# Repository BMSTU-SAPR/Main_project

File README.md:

## Main_project
Главный проект. Здесь будут собраны все работы

#Рыжков В.П. БМТ2-31М

## Отчет

Требуется создать схему электрическую-принципиальную платы, трассировку печатной платы и файлы платы для дальнейшего производства. Создание схемы происходит в программе KiCAD.

Плата будет основана на материалах, усвоенных в процессе прохождения курса и представлять из себя будет полосно-пропускающий фильтр на 2-х операционных усилителях. В целях возможности тестирования данной схемы при ее реальном производстве предусмотрены входы для осциллографа.

Поиск посадочных мест, УГО и 3D моделей элементов осуществлялось на сайтах https://www.snapeda.com/ и https://componentsearchengine.com/

В KiCAD были созданы отдельные библиотеки УГО и посадочных мест.

После этого с использованием новых компонентов была собрана схема электрической цепи (СЭП). Для стандартных элементов, таких как резисторы и конденсаторы, были выбраны площадки из библиотек KiCad. 

Затем проводим проверку получившейся СЭП и исправляем обнаруженные ошибки, связанные с подключением пинов, наличию "земли" у каждой микросхемы и др.

Собранная СЭП представлена на рис. 2.

Далее производим разводку печатной платы.

Далее нажимаем "Обновить печатную плату" и получаем печатную плату, после чего производим её разводку. Сначала соединяем контакты, не относящиеся к питанию и земле. Потом проводим питание, и в конце проводим землю. Для избежания перегрева и перегорания дорожек питания были рассчитаны ширины дорожек питания с помощью встроенного калькулятора для силы тока 0.5 Ампер. После проведения дорожек были скорректированы размеры печатной платы и произведена заливка платы GND с обеих сторон. При данной сложности схемы двуслойная плата - достаточна. Более того, оборотный ее слой задействовал в малой степени.

Для всех элементов платы, взятых с сайтов SnapEda и ComponentSearchEngine были выбраны 3D модели.

3D модель печатной платы представлена на следующих изображениях:

Рисунок 6 - Вид платы в 3д

Далее создаем гербер файлы и файлы сверловки.

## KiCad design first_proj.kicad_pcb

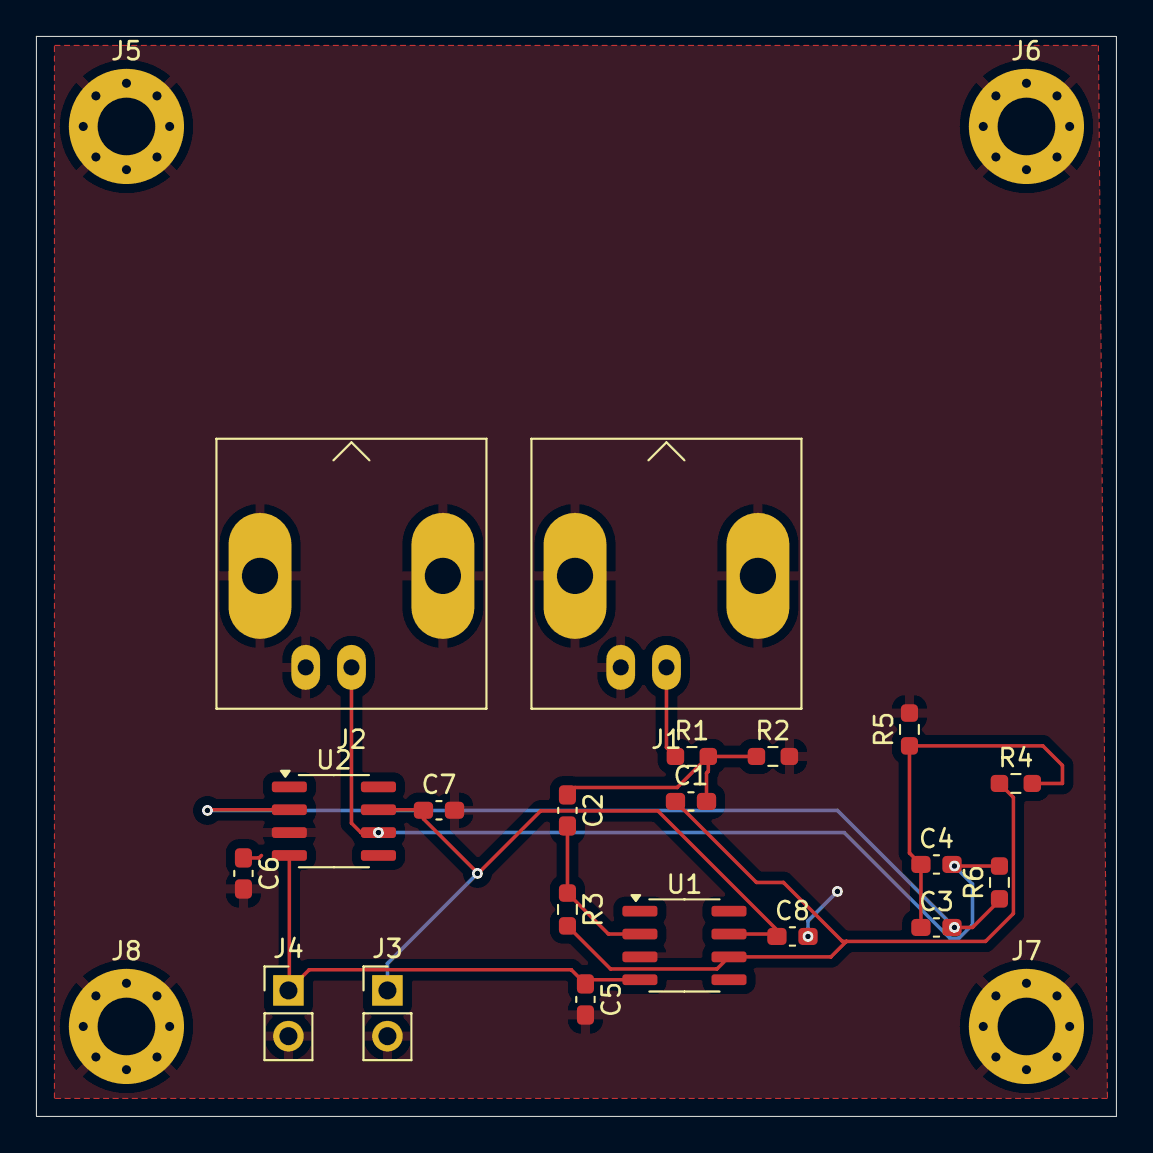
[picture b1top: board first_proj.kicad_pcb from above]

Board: 2 copper layers, 60.0 x 60.0 mm, 24 parts (0 on the bottom side), 10 nets.

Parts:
C1: 100p; C_0603_1608Metric_Pad1.08x0.95mm_HandSolder
C2, C3, C5, C6, C7, C8: 10n; C_0603_1608Metric_Pad1.08x0.95mm_HandSolder
C4: 12n; C_0603_1608Metric_Pad1.08x0.95mm_HandSolder
J1, J2: Conn_Coaxial; BNC_Amphenol_B6252HB-NPP3G-50_Horizontal
J3, J4: Conn_01x02; PinHeader_1x02_P2.54mm_Vertical
J5, J6, J7, J8: Screw_Terminal_01x01; MountingHole_3.2mm_M3_Pad_Via
R1: 1k; R_0603_1608Metric_Pad0.98x0.95mm_HandSolder
R2, R4: 10k; R_0603_1608Metric_Pad0.98x0.95mm_HandSolder
R3: 1.1k; R_0603_1608Metric_Pad0.98x0.95mm_HandSolder
R5, R6: 12k; R_0603_1608Metric_Pad0.98x0.95mm_HandSolder
U1, U2: OPA188xxD; SOIC-8_3.9x4.9mm_P1.27mm

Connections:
+5V: C7.1, C8.1, J3.1, U1.7 (V+), U2.7 (V+)
-5V: C5.1, J4.1, U1.4 (V-), U2.4 (V-)
GND: C5.2, C6.2, C7.2, C8.2, J1.2 (Ext), J2.2 (Ext), J3.2, J4.2, J5.1, J6.1, J7.1, J8.1, R2.2, R5.2, U1.3 (+), U2.3 (+)
unnamed: C1.1, R3.2, R4.1, U1.6
unnamed: C1.2, C2.1, R1.2, R2.1
unnamed: C3.1, C4.1, R4.2, R5.1
unnamed: J1.1 (In), R1.1
unnamed: C4.2, J2.1 (In), R6.2, U2.6
unnamed: C2.2, R3.1, U1.2 (-)
unnamed: C3.2, R6.1, U2.2 (-)

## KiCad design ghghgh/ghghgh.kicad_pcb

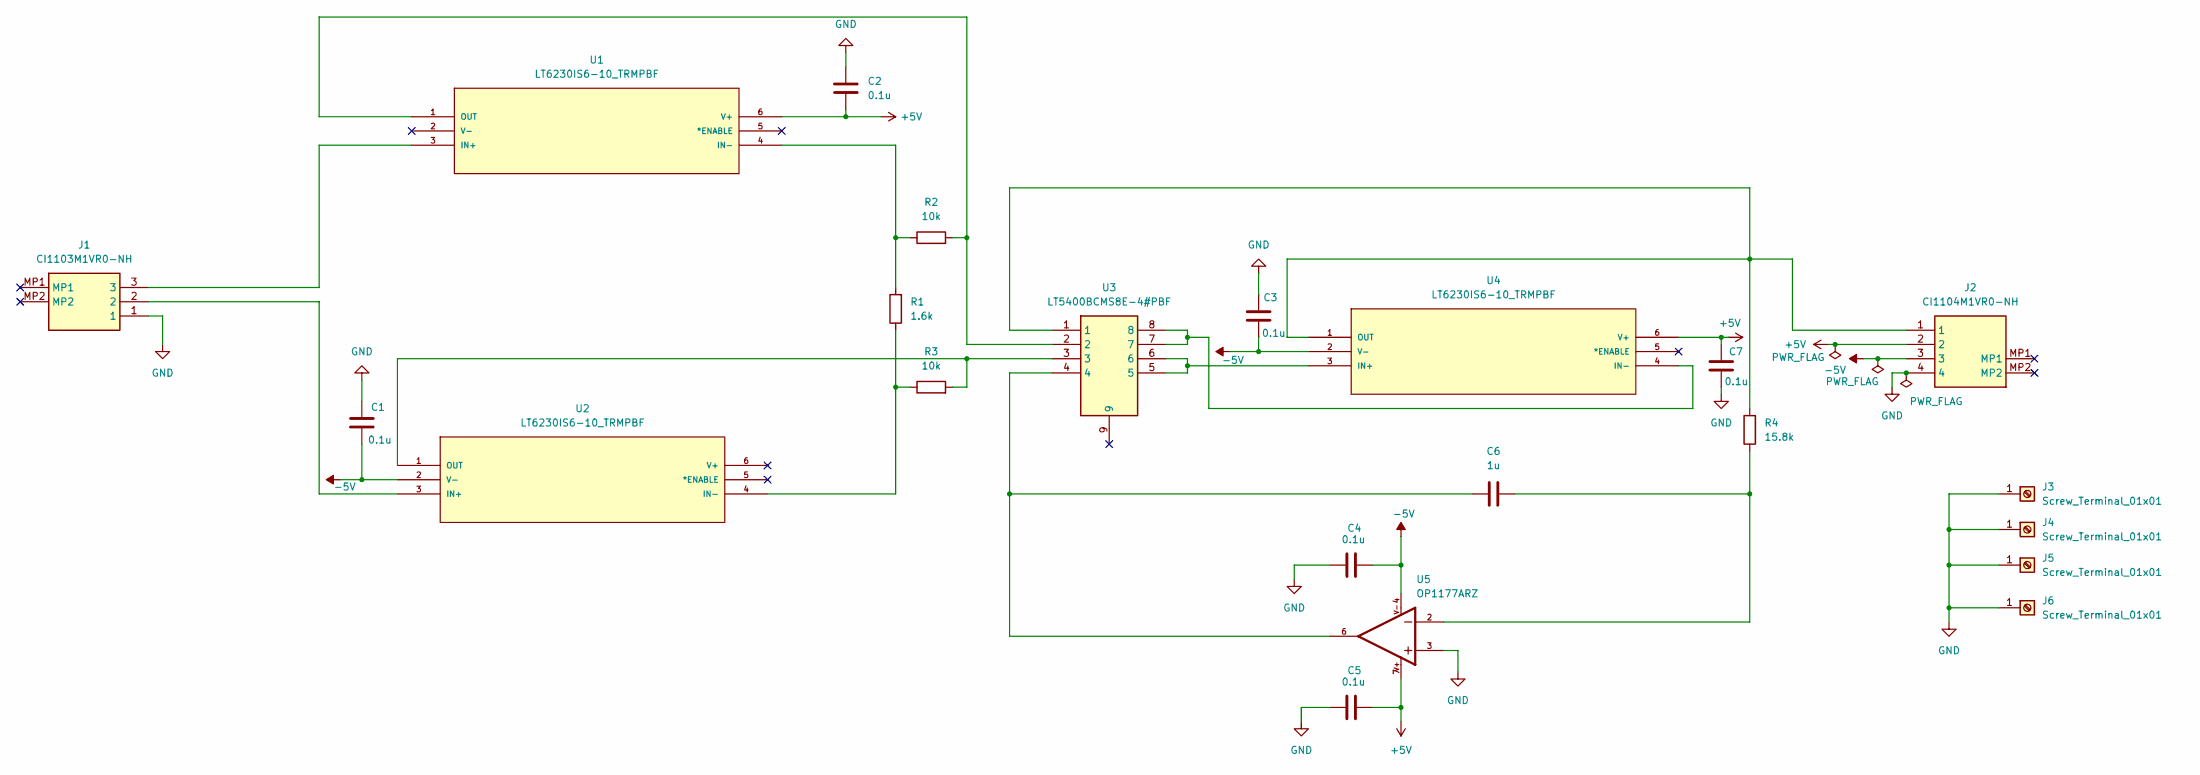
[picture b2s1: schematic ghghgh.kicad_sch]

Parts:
C1, C2, C3, C4, C5, C7: 0.1u; C_0201_0603Metric
C6: 1u; C_0201_0603Metric
J1: CI1103M1VR0-NH; CI1103M1VR0NH; Manufacturer_Part_Number CI1103M1VR0-NH
J2: CI1104M1VR0-NH; CI1104M1VR0NH; Manufacturer_Part_Number CI1104M1VR0-NH
J3, J4, J5, J6: Screw_Terminal_01x01; MountingHole_3mm_Pad_Via
R1: 1.6k; R_0201_0603Metric
R2, R3: 10k; R_0201_0603Metric
R4: 15.8k; R_0201_0603Metric
U1, U2, U4: LT6230IS6-10_TRMPBF; SOT-6_S
U3: LT5400BCMS8E-4#PBF; SOP65P490X110-9N; Manufacturer_Part_Number LT5400BCMS8E-4#PBF; Mouser Part Number 584-5400BCMS8E-4PBF
U5: OP1177ARZ; SO-8

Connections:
+5V: C2.1, C5.2, C7.2, J2.2, U1.6 (V+), U4.6 (V+), U5.7
-5V: C1.1, C3.1, C4.2, J2.3, U2.2 (V-), U4.2 (V-), U5.4
GND: C1.2, C2.2, C3.2, C4.1, C5.1, C7.1, J1.1, J2.4, J3.1, J4.1, J5.1, J6.1, U5.3
unnamed: C6.1, U3.4, U5.6
unnamed: C6.2, R4.1, U5.2
unnamed: J1.3, U1.3 (IN+)
unnamed: R1.2, R2.1, U1.4 (IN-)
unnamed: R2.2, U1.1 (OUT), U3.2
unnamed: J1.2, U2.3 (IN+)
unnamed: R1.1, R3.1, U2.4 (IN-)
unnamed: R3.2, U2.1 (OUT), U3.3
unnamed: U3.5, U3.6, U4.3 (IN+)
unnamed: U3.7, U3.8, U4.4 (IN-)
unnamed: J2.1, R4.2, U3.1, U4.1 (OUT)

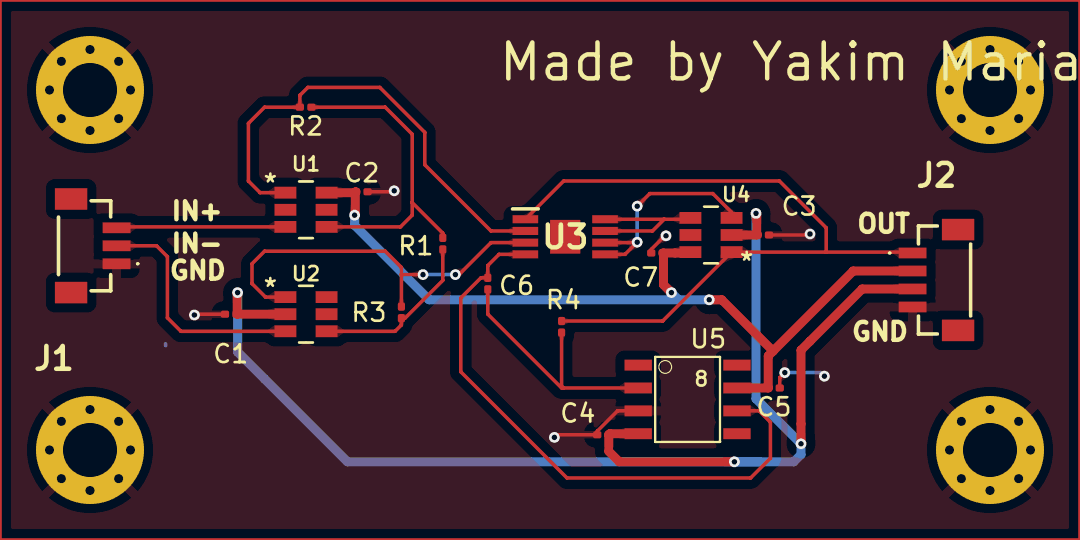
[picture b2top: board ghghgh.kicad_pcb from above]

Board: 2 copper layers, 22 parts (0 on the bottom side), 14 nets.

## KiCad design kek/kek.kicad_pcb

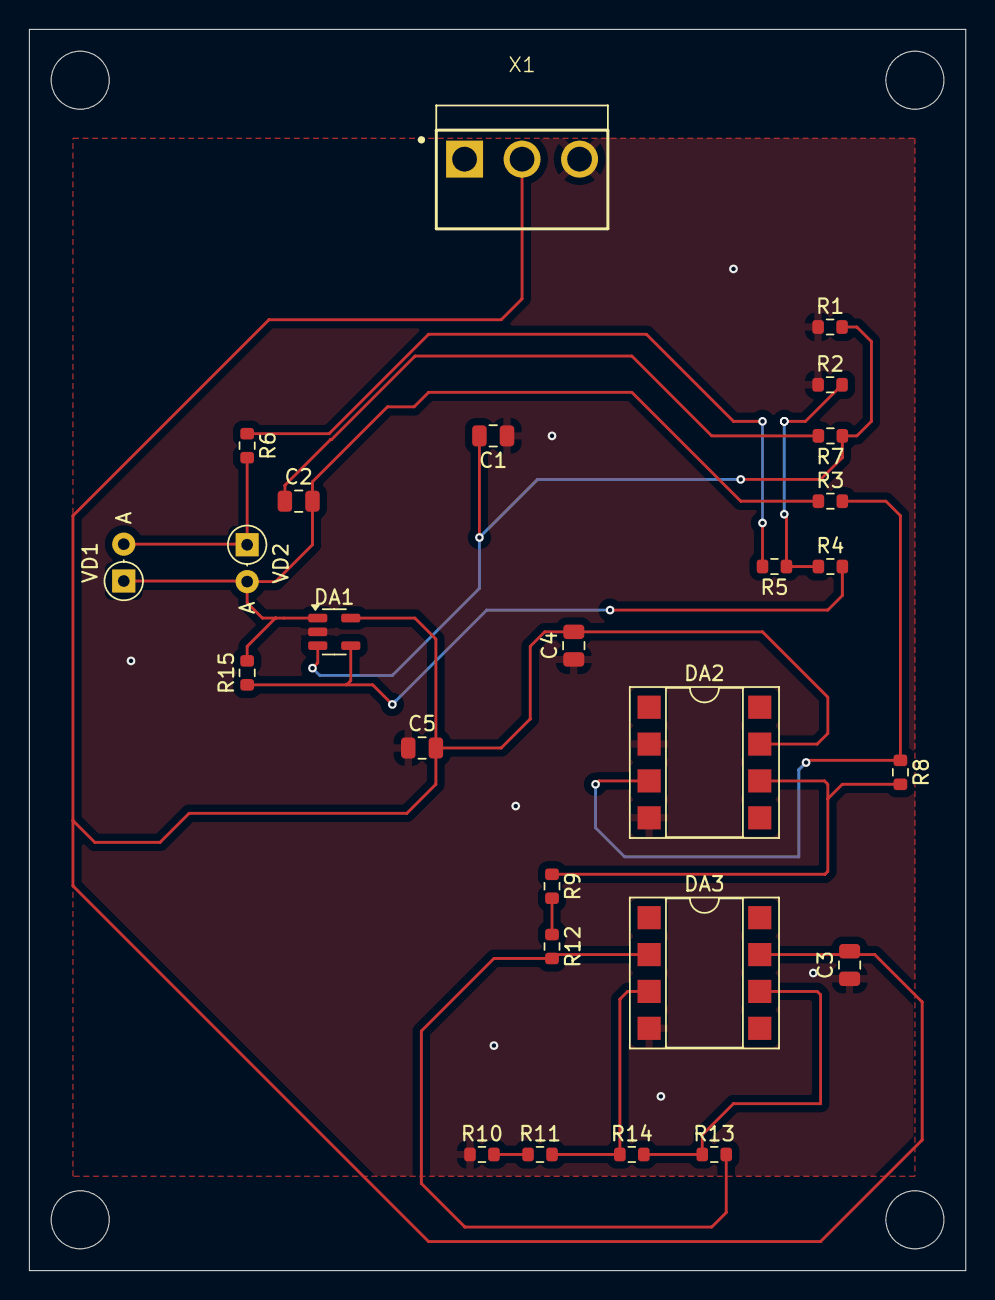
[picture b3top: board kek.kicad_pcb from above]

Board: 2 copper layers, 64.5 x 85.5 mm, 26 parts (0 on the bottom side), 16 nets.

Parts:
C1, C2: 750p; C_0805_2012Metric
C3, C4, C5: 0.1u; C_0805_2012Metric
DA1: AD8616; SOT-23-5
DA2, DA3: OP27; DIP-8_W7.62mm_SMDSocket_SmallPads
R1, R6, R7: 2.2k; R_0603_1608Metric
R2, R9, R10: 220; R_0603_1608Metric
R3: 10k; R_0603_1608Metric
R4: 100k; R_0603_1608Metric
R5: 160; R_0603_1608Metric
R8: 51k; R_0603_1608Metric
R11, R12: 5.1; R_0603_1608Metric
R13, R14: 1k; R_0603_1608Metric
R15: 220k; R_0603_1608Metric
VD1, VD2: 1N4148; D_DO-35_SOD27_P2.54mm_Vertical_AnodeUp
X1: B3P-VH

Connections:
+5V: C3.2, C4.2, C5.2, DA1.5 (V+), DA2.7 (V+), DA3.7 (V+), X1.2
/OUT1: C2.2, DA1.1 (OUT), R3.1, R15.2, VD1.1, VD2.2
/OUT2: DA2.6 (OUT), R8.2, R9.1
Earth: C1.1, C3.1, C4.1, C5.1, DA1.2 (V-), DA2.2 (IN+), DA2.4 (V-), DA3.4 (V-), R1.1, R2.1, R10.1, X1.3
unnamed: C2.1, R7.2
unnamed: C1.2, DA1.3 (IN+), R1.2, R7.1
unnamed: DA1.4 (IN-), R4.2, R15.1
unnamed: DA2.3 (IN-), R3.2, R8.1
unnamed: DA3.2 (IN+), R12.2, R13.2
unnamed: DA3.3 (IN-), R11.2, R14.1
unnamed: DA3.6 (OUT), R13.1, R14.2
unnamed: R2.2, R4.1, R5.1
unnamed: R5.2, R6.1
unnamed: R6.2, VD1.2, VD2.1
unnamed: R10.2, R11.1
unnamed: R9.2, R12.1

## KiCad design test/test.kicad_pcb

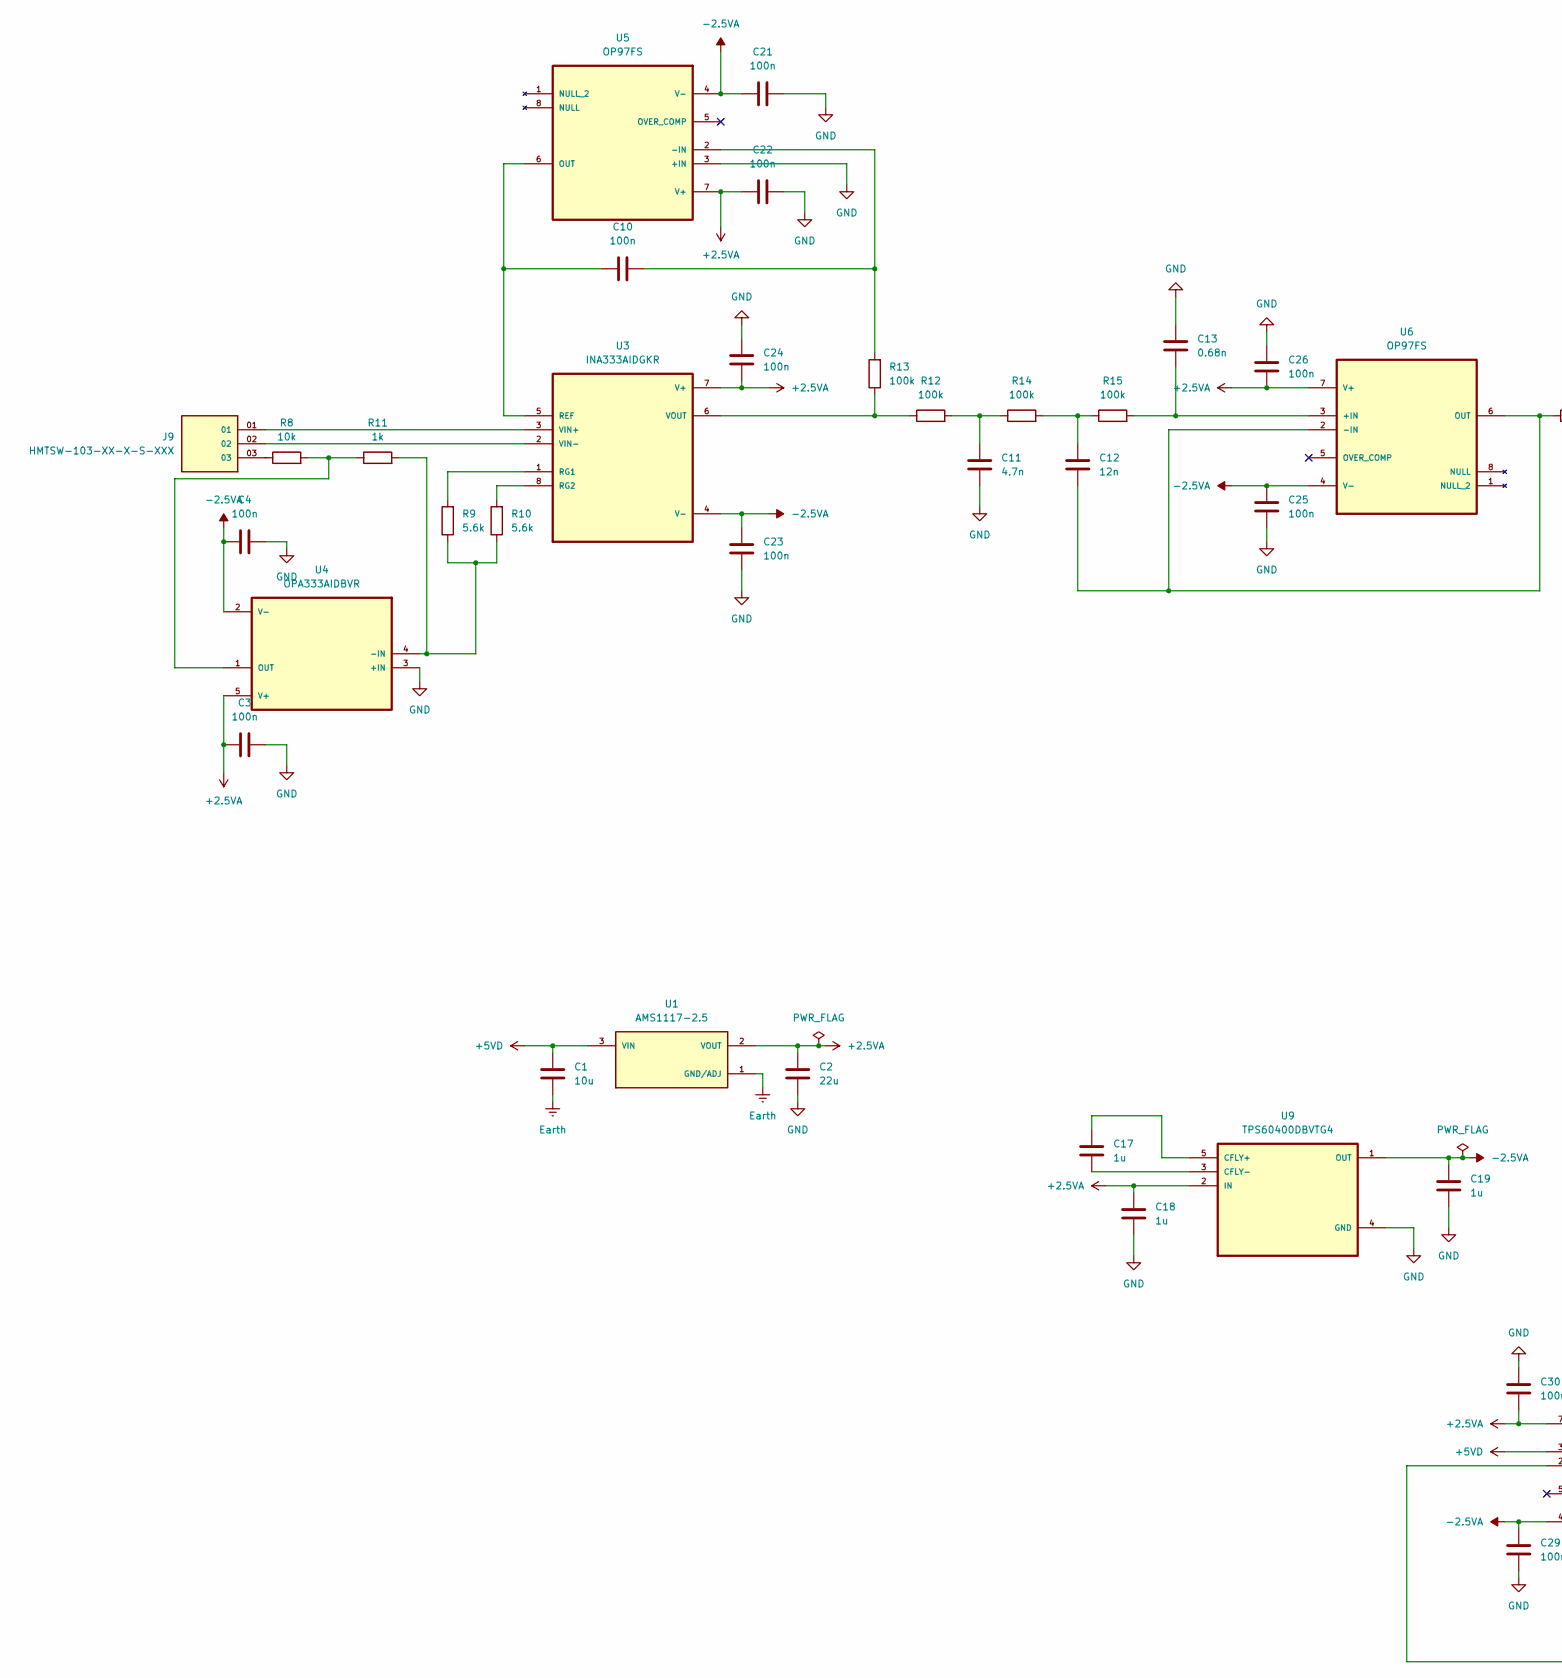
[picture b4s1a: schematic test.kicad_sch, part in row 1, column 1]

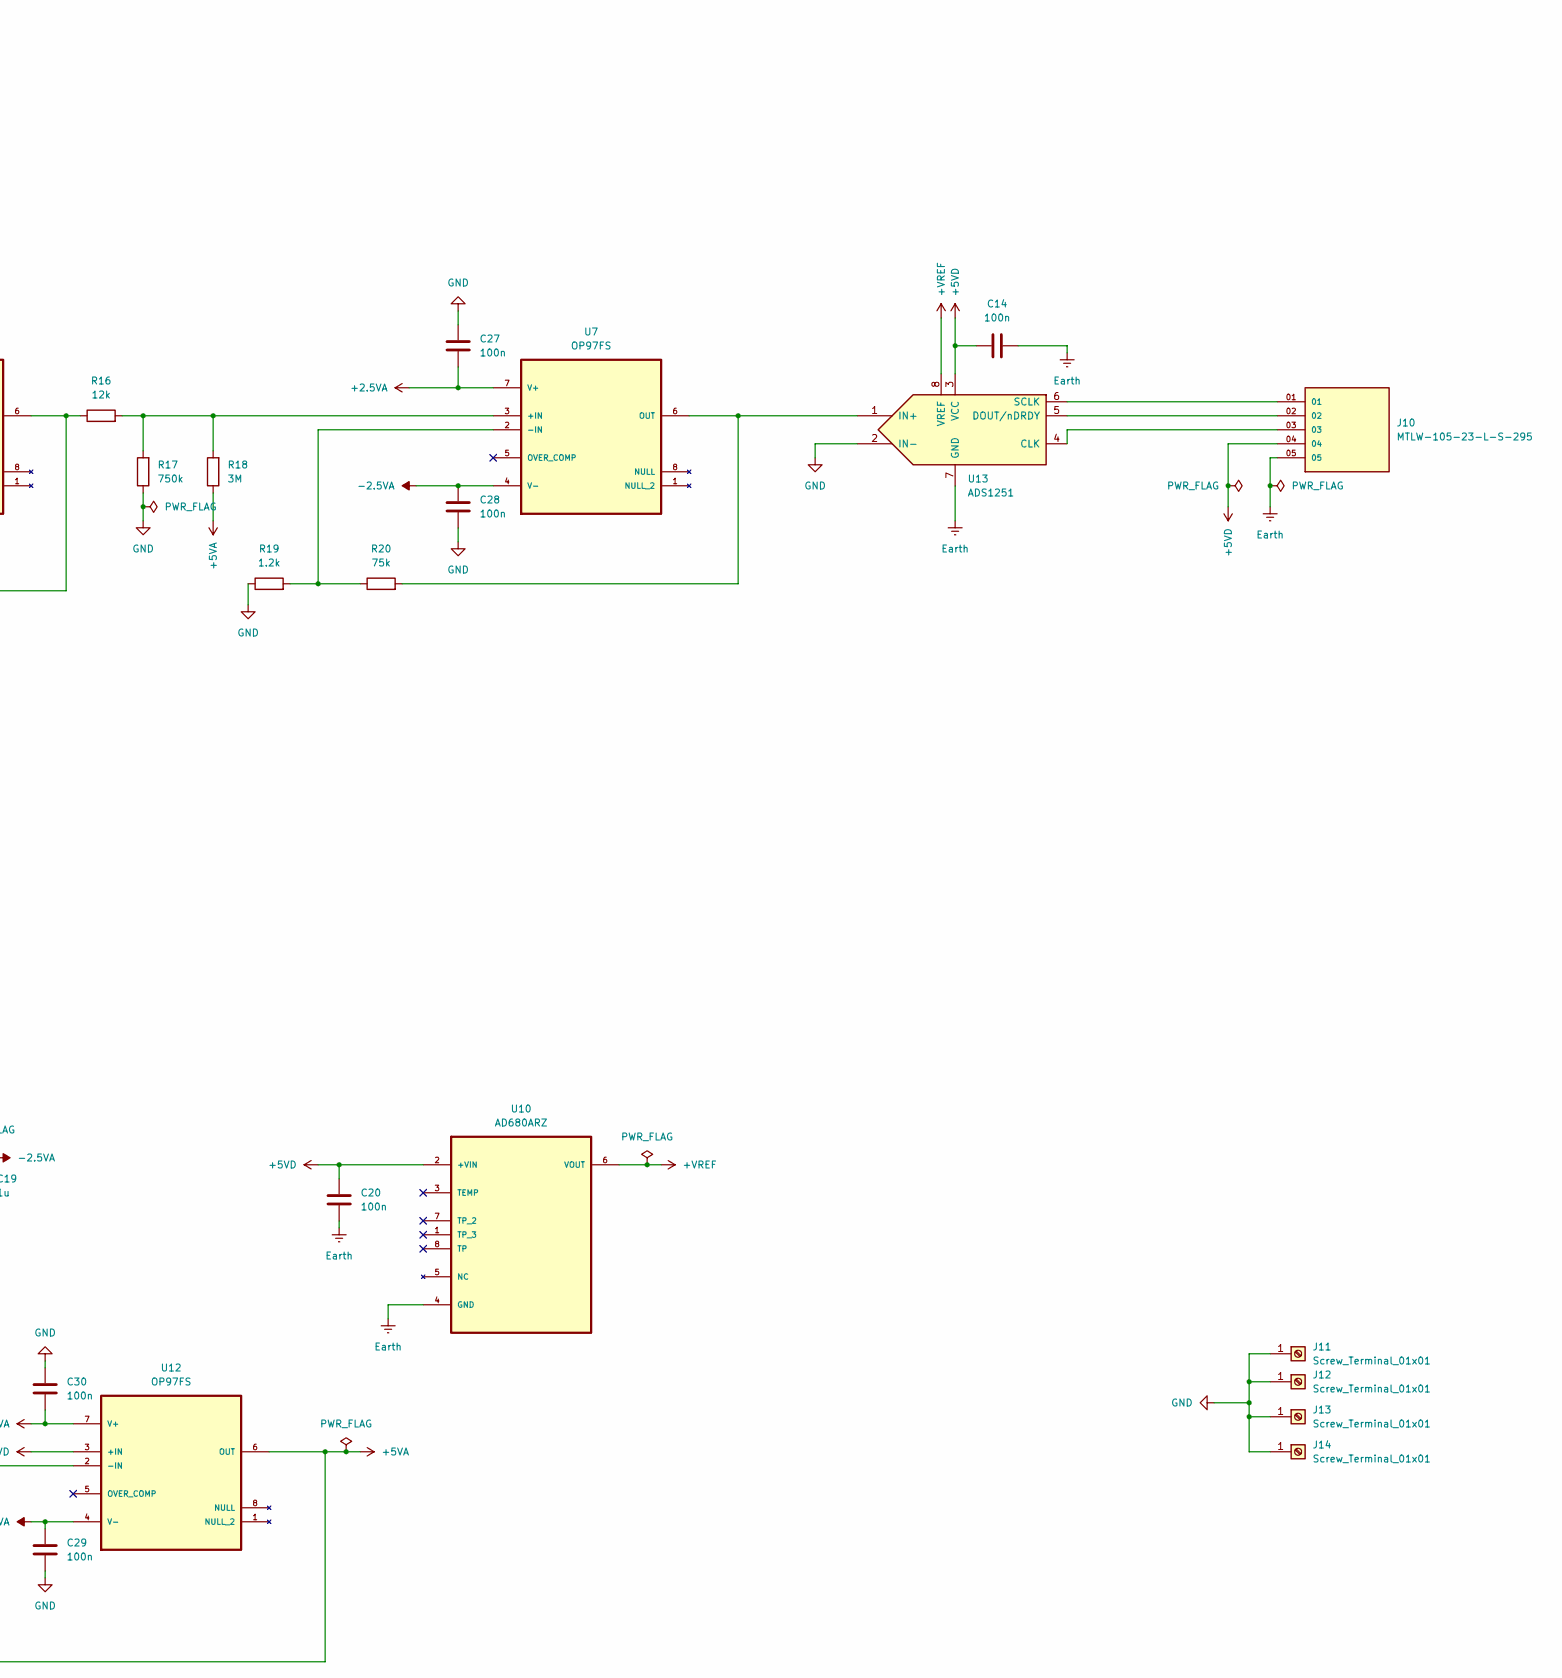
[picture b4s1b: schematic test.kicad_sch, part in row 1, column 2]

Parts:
C1: 10u; C_0201_0603Metric
C2: 22u; C_0201_0603Metric
C3, C4, C10, C14, C20, C21, C22, C23, C24, C25, C26, C27, C28, C29, C30: 100n; C_0201_0603Metric
C11: 4.7n; C_0201_0603Metric
C12: 12n; C_0201_0603Metric
C13: 0.68n; C_0201_0603Metric
C17, C18, C19: 1u; C_0201_0603Metric
J9: HMTSW-103-XX-X-S-XXX; SAMTEC_HMTSW-103-XX-X-S-XXX; PARTREV A
J10: MTLW-105-23-L-S-295; SAMTEC_MTLW-105-23-L-S-295; PARTREV R
J11, J12, J13, J14: Screw_Terminal_01x01; MountingHole_3.2mm_M3_Pad_Via
R8: 10k; R_0201_0603Metric
R9, R10: 5.6k; R_0201_0603Metric
R11: 1k; R_0201_0603Metric
R12, R13, R14, R15: 100k; R_0201_0603Metric
R16: 12k; R_0201_0603Metric
R17: 750k; R_0201_0603Metric
R18: 3M; R_0201_0603Metric
R19: 1.2k; R_0201_0603Metric
R20: 75k; R_0201_0603Metric
U1: AMS1117-2.5; SOT229P700X180-4N; PARTREV N/A
U3: INA333AIDGKR; SOP65P490X110-8N
U4: OPA333AIDBVR; SOT95P280X145-5N
U5, U6, U7, U12: OP97FS; SOIC127P600X175-8N-1; MPN OP97FS
U9: TPS60400DBVTG4; SOT95P280X145-5N
U10: AD680ARZ; SOIC127P600X175-8N; MPN AD680ARZ
U13: ADS1251; SOIC-8_3.9x4.9mm_P1.27mm

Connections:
+2.5VA: C2.2, C3.1, C18.2, C22.1, C24.1, C26.1, C27.1, C30.1, U1.2 (VOUT), U3.7 (V+), U4.5 (V+), U5.7 (V+), U6.7 (V+), U7.7 (V+), U9.2 (IN), U12.7 (V+)
+5VA: R18.1, U12.2 (-IN), U12.6 (OUT)
+5VD: C1.2, C14.1, C20.2, J10.04, U1.3 (VIN), U10.2 (+VIN), U12.3 (+IN), U13.3 (VCC)
+VREF: U10.6 (VOUT), U13.8 (VREF)
-2.5VA: C4.1, C19.2, C21.1, C23.2, C25.2, C28.2, C29.2, U3.4 (V-), U4.2 (V-), U5.4 (V-), U6.4 (V-), U7.4 (V-), U9.1 (OUT), U12.4 (V-)
Earth: C1.1, C14.2, C20.1, J10.05, U1.1 (GND/ADJ), U10.4 (GND), U13.7 (GND)
GND: C2.1, C3.2, C4.2, C11.1, C13.2, C18.1, C19.1, C21.2, C22.2, C23.1, C24.2, C25.1, C26.2, C27.2, C28.1, C29.1, C30.2, J11.1, J12.1, J13.1, J14.1, R17.1, R19.1, U4.3 (+IN), U5.3 (+IN), U9.4 (GND), U13.2 (IN-)
unnamed: C11.2, R12.2, R14.1
unnamed: C12.2, R14.2, R15.1
unnamed: J9.03, R8.1
unnamed: C10.1, U3.5 (REF), U5.6 (OUT)
unnamed: R9.2, U3.1 (RG1)
unnamed: R10.2, U3.8 (RG2)
unnamed: J9.01, U3.3 (VIN+)
unnamed: J9.02, U3.2 (VIN-)
unnamed: R12.1, R13.1, U3.6 (VOUT)
unnamed: R9.1, R10.1, R11.2, U4.4 (-IN)
unnamed: R8.2, R11.1, U4.1 (OUT)
unnamed: C10.2, R13.2, U5.2 (-IN)
unnamed: C13.1, R15.2, U6.3 (+IN)
unnamed: C12.1, R16.1, U6.2 (-IN), U6.6 (OUT)
unnamed: R16.2, R17.2, R18.2, U7.3 (+IN)
unnamed: R19.2, R20.1, U7.2 (-IN)
unnamed: C17.2, U9.5 (CFLY+)
unnamed: C17.1, U9.3 (CFLY-)
unnamed: J10.03, U13.4 (CLK)
unnamed: J10.02, U13.5 (DOUT/nDRDY)
unnamed: R20.2, U7.6 (OUT), U13.1 (IN+)
unnamed: J10.01, U13.6 (SCLK)

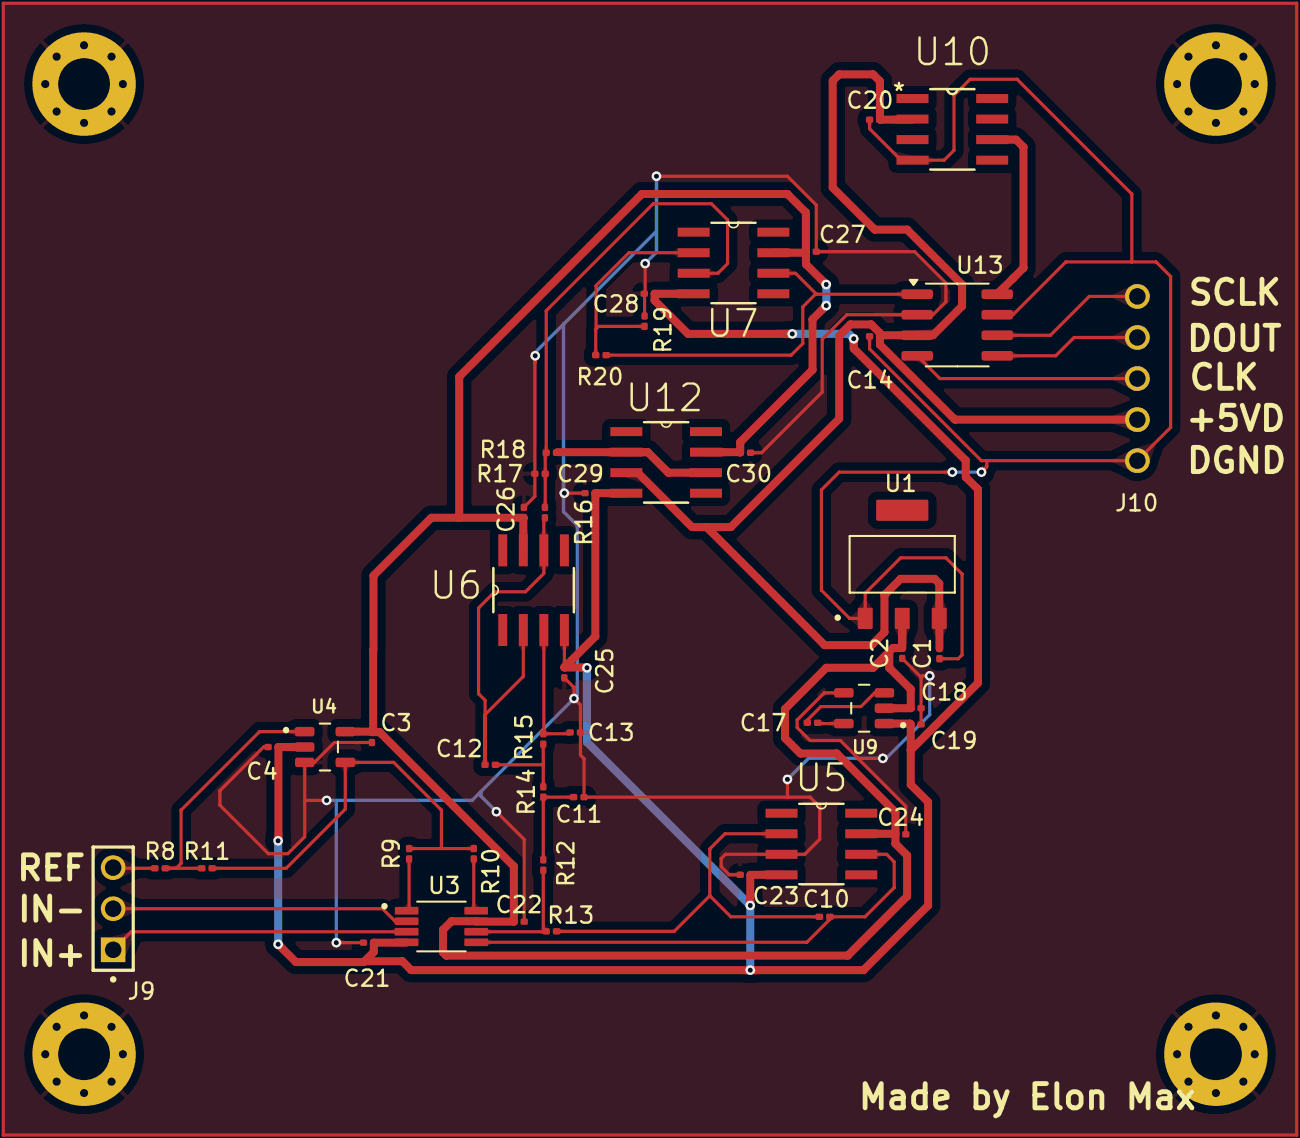
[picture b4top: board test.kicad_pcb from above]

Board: 2 copper layers, 52 parts (1 on the bottom side), 29 nets.

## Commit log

2024-09-26 Added KiCad_lib
2024-09-26 text
2024-09-26 I love KiCad
2024-09-26 boze moy
2024-09-26 helpme
2024-09-26 Worked with libraries
2024-09-26 work work work
2024-09-26 Yard work
2024-09-26 Work with LBB
2024-09-26 Nothing important
2024-10-01 lool
2024-10-02 first task
2024-10-03 Added schematic v1
2024-10-03 Updated lib
2024-10-03 Schematic done
2024-10-03 Я молодец
2024-10-10 PCB tracing done
2024-10-11 Added pechatnaya plata
2024-10-16 enter new files
2024-10-16 new files
2024-10-17 dorow
2024-10-17 perviy commit comom
2024-10-27 Changed md
2024-10-29 erifgerifger
2024-10-29 Done
2024-10-30 Update README.md
    отчет
2024-10-30 герберы
    герберы агрегатора
2024-10-30 Create Gerbers
2024-10-30 Changed md and added images to folder
2024-10-31 My commit
2024-10-31 Отчет
2024-10-31 New commit
2024-10-31 Adding files without dirs
2024-10-31 everything else with needed directories
2024-10-31 now everything with otchyot
